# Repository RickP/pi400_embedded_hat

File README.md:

# pi400_embedded_hat
A very simple "hat" for the pi 400 that helps with embedded development. Gives easy access to en SWD port, I2C, SPI and UART.

Work in progress!

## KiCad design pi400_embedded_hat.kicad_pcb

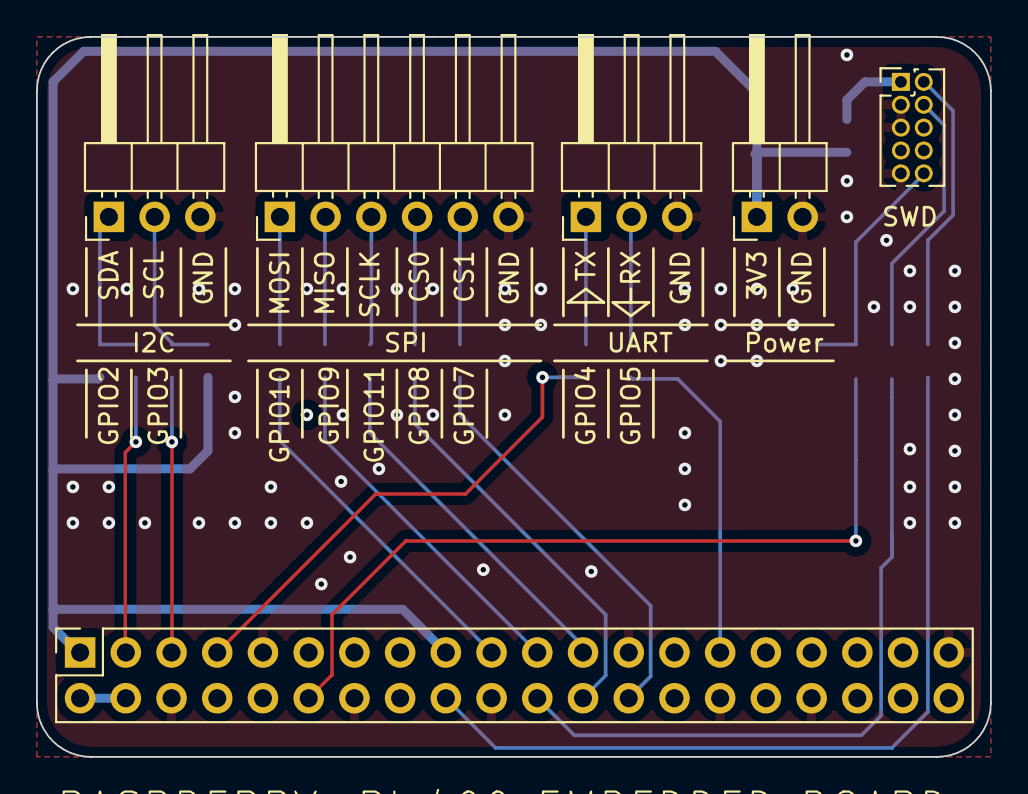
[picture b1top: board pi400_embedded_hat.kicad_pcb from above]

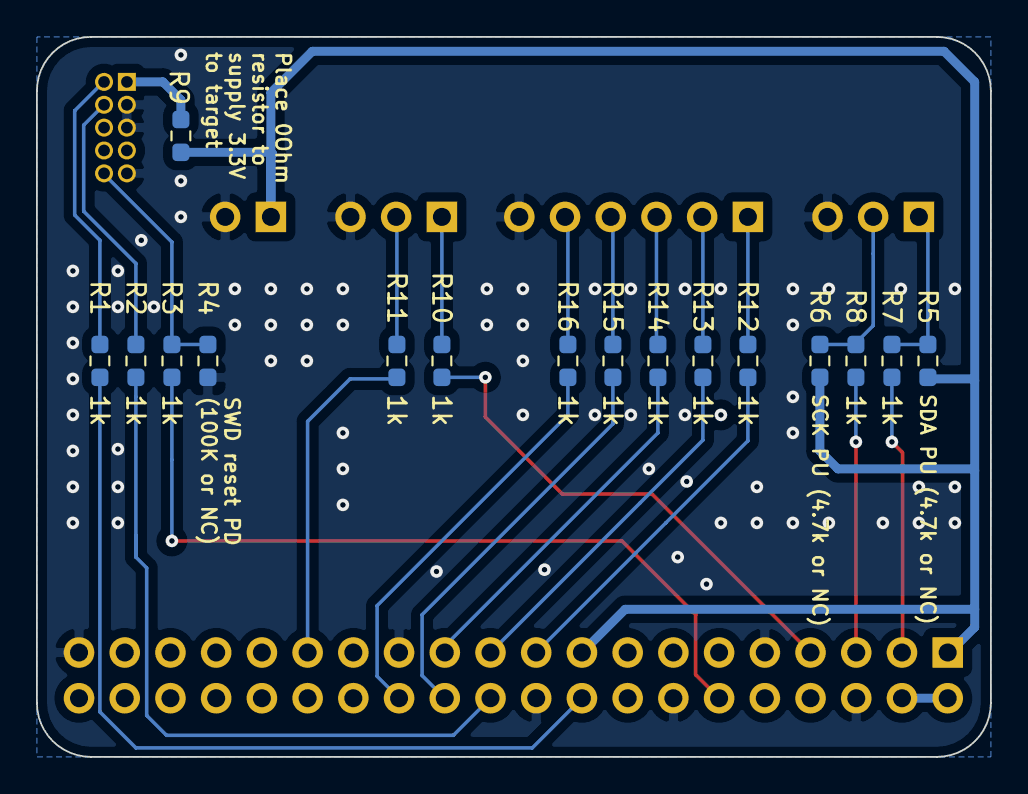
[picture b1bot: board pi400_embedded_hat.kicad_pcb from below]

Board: 2 copper layers, 53.0 x 40.0 mm, 22 parts (16 on the bottom side), 28 nets.

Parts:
J1: Conn_02x20_Odd_Even; PinSocket_2x20_P2.54mm_Vertical
J2: Conn_02x05_Odd_Even; PinHeader_2x05_P1.27mm_Vertical
J3, J4: Conn_01x03_Male; PinHeader_1x03_P2.54mm_Horizontal
J5: Conn_01x02_Male; PinHeader_1x02_P2.54mm_Horizontal
J6: Conn_01x06_Male; PinHeader_1x06_P2.54mm_Horizontal
R1, R2, R3, R7, R8, R10, R11, R12, R13, R14, R15, R16: 1k; R_0603_1608Metric_Pad0.98x0.95mm_HandSolder
R4: 100k; R_0603_1608Metric_Pad0.98x0.95mm_HandSolder
R5, R6: 4.7k; R_0603_1608Metric_Pad0.98x0.95mm_HandSolder
R9: 0R; R_0603_1608Metric_Pad0.98x0.95mm_HandSolder

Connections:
+3V3: J1.1, J1.17, J5.1, R5.2, R6.1, R9.2
+5V: J1.2, J1.4
/GPIO2(SDA1): J1.3, R7.1
/GPIO3(SCL1): J1.5, R8.1
/GPIO4(GCLK): J1.7, R10.1
/GPIO5: J1.29, R11.1
/GPIO7(SPI1_CE_N): J1.26, R16.1
/GPIO8(SPI0_CE_N): J1.24, R15.1
/GPIO9(SPI0_MISO): J1.21, R13.1
/GPIO10(SPI0_MOSI): J1.19, R12.1
/GPIO11(SPI0_SCK): J1.23, R14.1
/GPIO18(GEN1)(PWM0): J1.12, R3.1
/GPIO24(GEN5): J1.18, R1.1
/GPIO25(GEN6): J1.22, R2.1
GND: J1.6, J1.9, J1.14, J1.20, J1.25, J1.30, J1.34, J1.39, J2.3, J2.5, J2.9, J3.3, J4.3, J5.2, J6.6, R4.1
unnamed: J2.1, R9.1
unnamed: J2.2, R1.2
unnamed: J2.4, R2.2
unnamed: J2.10, R3.2, R4.2
unnamed: J3.1, R5.1, R7.2
unnamed: J3.2, R6.2, R8.2
unnamed: J4.1, R10.2
unnamed: J4.2, R11.2
unnamed: J6.1, R12.2
unnamed: J6.2, R13.2
unnamed: J6.3, R14.2
unnamed: J6.4, R15.2
unnamed: J6.5, R16.2

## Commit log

2020-11-23 init
